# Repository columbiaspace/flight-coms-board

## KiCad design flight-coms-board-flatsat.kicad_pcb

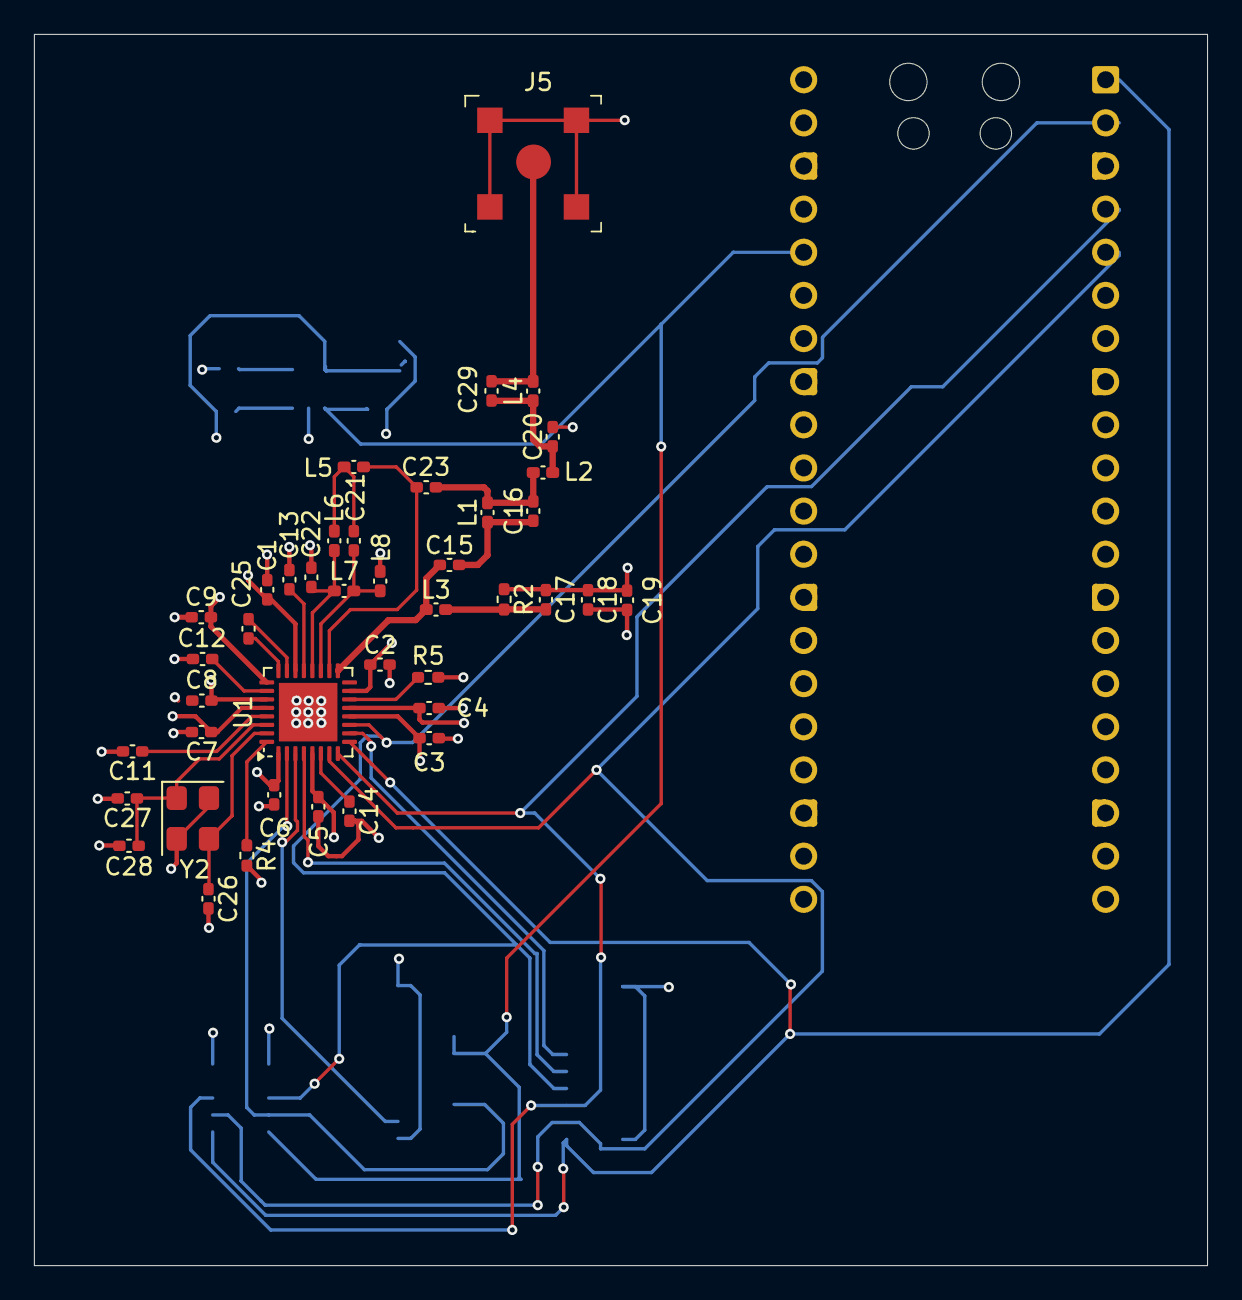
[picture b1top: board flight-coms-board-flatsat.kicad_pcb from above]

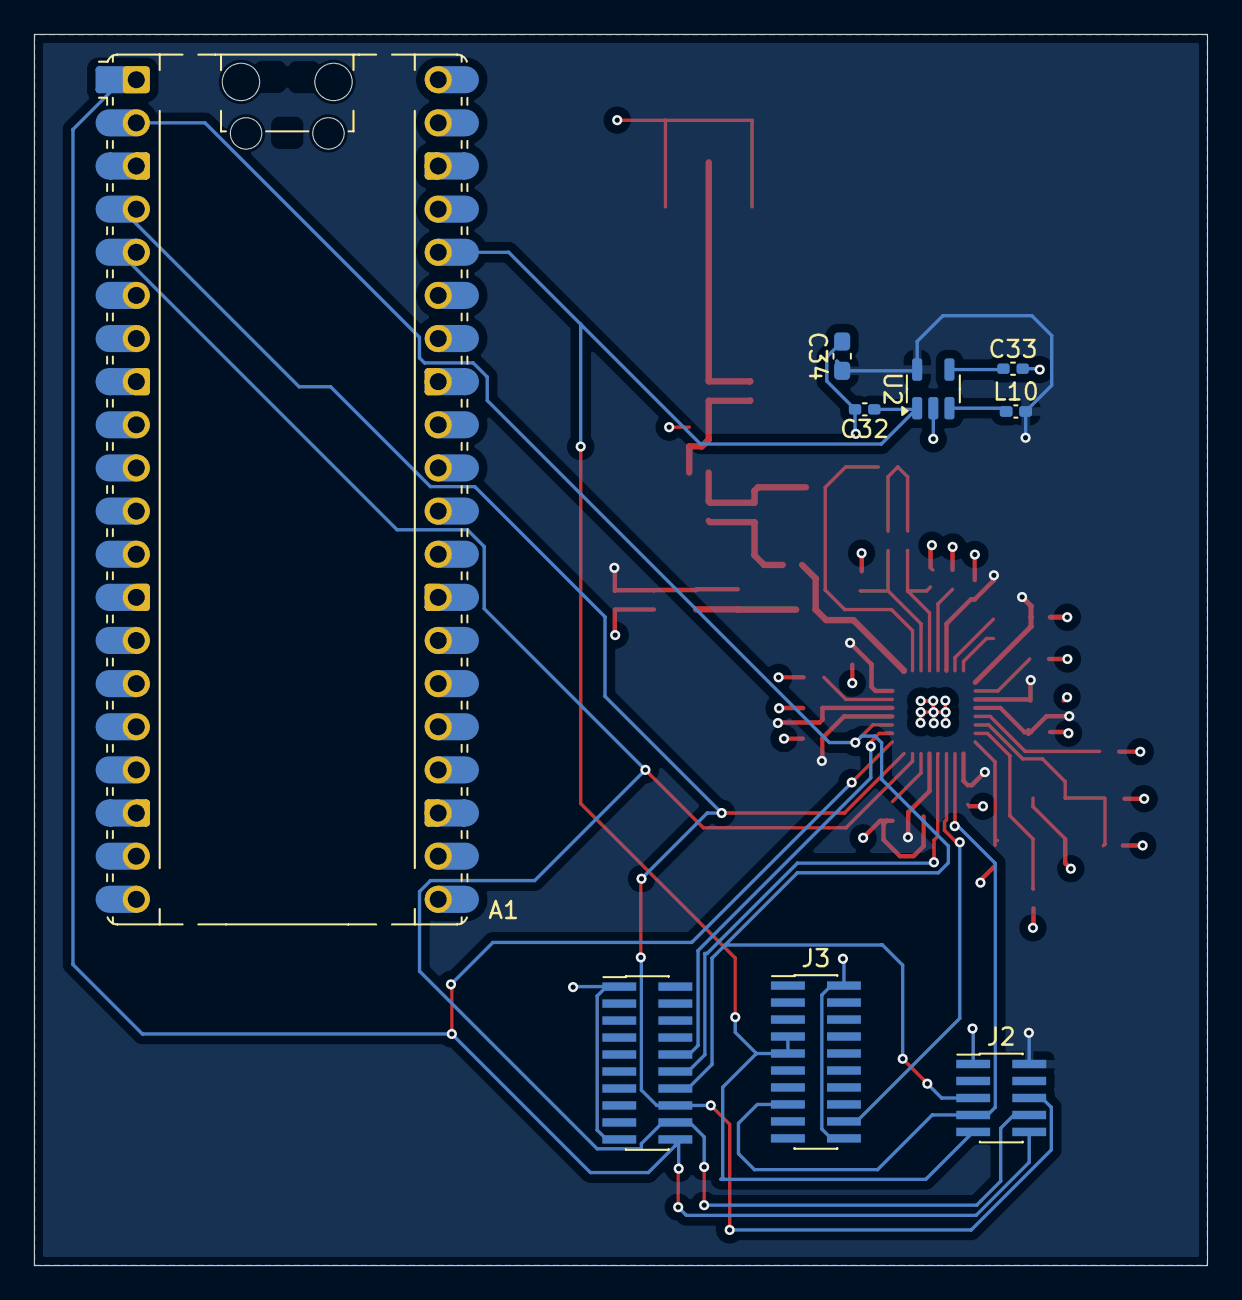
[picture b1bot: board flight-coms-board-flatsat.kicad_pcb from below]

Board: 4 copper layers, 69.1 x 72.5 mm, 50 parts (9 on the bottom side), 33 nets.

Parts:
A1: RaspberryPi_Pico; RaspberryPi_Pico_Common_Unspecified
C1, C2, C3, C4, C5, C6, C7, C8, C9, C11, C12: 47nF; C_0402_1005Metric_Pad0.74x0.62mm_HandSolder
C13, C18: 10nF; C_0402_1005Metric_Pad0.74x0.62mm_HandSolder
C14: 220nF; C_0402_1005Metric_Pad0.74x0.62mm_HandSolder
C15: 39pF; C_0402_1005Metric_Pad0.74x0.62mm_HandSolder
C16: 2.2pF; C_0402_1005Metric_Pad0.74x0.62mm_HandSolder
C17: 56pF; C_0402_1005Metric_Pad0.74x0.62mm_HandSolder
C19: 100pF; C_0402_1005Metric_Pad0.74x0.62mm_HandSolder
C20: 6.2pF; C_0402_1005Metric_Pad0.74x0.62mm_HandSolder
C21, C22, C23: 5.1pF; C_0402_1005Metric_Pad0.74x0.62mm_HandSolder
C25: 1.5nF; C_0402_1005Metric_Pad0.74x0.62mm_HandSolder
C26, C27: 15pF; C_0402_1005Metric_Pad0.74x0.62mm_HandSolder
C28, C29, C32, C33: DNM_0402; C_0402_1005Metric_Pad0.74x0.62mm_HandSolder
C34: 2.2uF; C_0603_1608Metric_Pad1.08x0.95mm_HandSolder
J2: Conn_02x05_Odd_Even; PinHeader_2x05_P1.00mm_Vertical_SMD
J3, J4: Conn_02x10_Odd_Even; PinHeader_2x10_P1.00mm_Vertical_SMD
J5: CONSMA001-SMD-G; RF_SMA_Receptical_Vertical_CONSMA001-SMD-G
L1, L5: 15nH; L_0402_1005Metric_Pad0.77x0.64mm_HandSolder
L2: 43nH; L_0402_1005Metric_Pad0.77x0.64mm_HandSolder
L3, L7: 56nH; L_0402_1005Metric_Pad0.77x0.64mm_HandSolder
L4: 22nH; L_0402_1005Metric_Pad0.77x0.64mm_HandSolder
L6, L8: 27nH; L_0402_1005Metric_Pad0.77x0.64mm_HandSolder
L10: BLM15HG102SN1; L_0402_1005Metric_Pad0.77x0.64mm_HandSolder
R2: 18; R_0402_1005Metric_Pad0.72x0.64mm_HandSolder
R4: 0; R_0402_1005Metric_Pad0.72x0.64mm_HandSolder
R5: 56k; R_0402_1005Metric_Pad0.72x0.64mm_HandSolder
U1: CC1200; QFN-32-1EP_5x5mm_P0.5mm_EP3.45x3.45mm
U2: TPS79330-EP; SOT-23-5
Y2: 40MHz; Oscillator_SMD_SeikoEpson_SG8002CE-4Pin_3.2x2.5mm

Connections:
/3V3: A1.36 (3V3), C32.1, J2.9, J3.7, J3.9, U2.1 (IN)
/CSN: A1.2 (GPIO1), J2.5, J4.14, U1.11 (~CS)
/GPIO0: J4.10, U1.10 (GPIO0)
/GPIO2: J4.12, U1.4 (GPIO2)
/GPIO3: J3.18, U1.3 (GPIO3)
/MISO: A1.1 (GPIO0), J2.10, J4.20, U1.9 (SO(GPIO1))
/MOSI: A1.5 (GPIO3), J2.8, J4.18, U1.7 (SI)
/RESET: J2.7, J3.15, U1.2 (~RESET)
/SCLK: A1.4 (GPIO2), J2.6, J4.16, U1.8 (SCLK)
/VDD_REG: C1.1, C2.1, C3.1, C4.1, C5.1, C6.1, C7.1, C8.1, C9.1, C17.1, C18.1, C19.1, C34.1, J2.2, L10.2, R2.1, U1.1 (VDD_GUARD), U1.5 (DVDD), U1.12 (DVDD), U1.13 (AVDD_IF), U1.15 (AVDD_RF), U1.22 (AVDD_SYNTH1), U1.25 (AVDD_PFD_CHP), U1.27 (AVDD_SYNTH2), U1.28 (AVDD_XOSC), U2.5 (OUT)
GND: A1.3 (GND), A1.8 (GND), A1.13 (GND), A1.18 (GND), A1.23 (GND), A1.28 (GND), A1.38 (GND), C1.2, C2.2, C3.2, C4.2, C5.2, C6.2, C7.2, C8.2, C9.2, C11.2, C12.2, C13.2, C14.2, C18.2, C19.2, C20.2, C22.2, C26.2, C27.2, C28.1, C32.2, C33.2, C34.2, J2.1, J3.2, J3.20, J4.1, J4.19, J5.1, L8.2, R4.2, R5.1, U1.33 (GND_EP), U2.2 (GND), Y2.2, Y2.4
unnamed: C15.2, C16.1, L1.1
unnamed: C16.2, C23.2, L1.2, L2.1
unnamed: C17.2, L3.2, R2.2
unnamed: C20.1, C29.1, L2.2, L4.1
unnamed: C21.1, L5.2, L6.1
unnamed: C29.2, J5.2, L4.2
unnamed: C14.1, U1.6 (DCPL)
unnamed: C12.1, U1.26 (DCPL_PFD_CHP)
unnamed: C13.1, U1.21 (DCPL_VCO)
unnamed: C11.1, U1.29 (DCPL_XOSC)
unnamed: R4.1, U1.32 (EXT_XOSC)
unnamed: C22.1, L6.2, L7.1, U1.20 (LNA_N)
unnamed: C21.2, L7.2, L8.1, U1.19 (LNA_P)
unnamed: C25.2, U1.23 (LPF0)
unnamed: C25.1, U1.24 (LPF1)
unnamed: C15.1, L3.1, U1.17 (PA)
unnamed: R5.2, U1.14 (RBIAS)
unnamed: C23.1, L5.1, U1.18 (TRX_SW)
unnamed: C27.1, C28.2, U1.30 (XOSC_Q1), Y2.1
unnamed: C26.1, U1.31 (XOSC_Q2), Y2.3
unnamed: C33.1, U2.4 (BP)
unnamed: L10.1, U2.3 (EN)

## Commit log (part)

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2026-03-18 schematic
2026-03-18 reference schematic
2026-04-16 Minor fixes and changes
2026-04-17 Flipped pico footprint for USB clearance
